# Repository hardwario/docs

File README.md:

# HARDWARIO Documentation

Technical documentation for HARDWARIO products and services —
[docs.hardwario.com](https://docs.hardwario.com). Built with
[Docusaurus 3](https://docusaurus.io). A multi-instance site: each product has its
own doc set served under `/<product>/`.

## Tech stack

- **Docusaurus 3** — React + MDX static site generator
- **Multi-instance docs** — one `@docusaurus/plugin-content-docs` instance per product
- **Algolia DocSearch** — site-wide search (index `hardwario`)
- **Cloudflare Workers** — hosting (static assets, auto-deploy via Workers Builds)

## Develop

```bash
npm install        # first time / after dependency changes (Node 18+)
npm start          # dev server → http://localhost:3000, hot reload
npm run build      # production build → build/ (fails on broken links)
npm run serve      # serve the production build locally
npm run clear      # clear the Docusaurus cache
```

## Project structure

```
docusaurus.config.js     # site config: presets, plugin instances, navbar, footer, Algolia, theme
sidebars-<product>.js    # one sidebar per product instance
<product>/               # one content folder per product, served at /<product>/:
                         #   chester, sticker, ember, fiber, gauger, tapper, tower,
                         #   cloud, cloud-new, apps, milesight, glider, rakwireless
src/
  pages/index.js         # custom homepage
  css/custom.css         # global styles / CSS variables
static/                  # assets; reference images by absolute path (/img/…)
                         #   incl. static/_redirects (same-domain slug redirects)
wrangler.jsonc           # Cloudflare Worker config — serves build/ as static assets
```

The main preset is the `chester` instance; the others are configured in the
`plugins` array of `docusaurus.config.js`. See the `docusaurus-sites` skill in the
website-admin repo for the multi-instance details.

## Content

- Docs are **Markdown/MDX** inside the relevant `<product>/` directory — identify
  the right folder first, then preserve frontmatter.
- Add new pages to the matching `sidebars-<product>.js`.
- Internal links are relative within a product; cross-product links use absolute
  paths (e.g. `/cloud/api`). **Broken internal links fail the build**
  (`onBrokenLinks: 'throw'`).
- Images live in `static/`, referenced as `/img/…`; the ideal-image and
  image-zoom plugins handle optimization and click-to-zoom.
- Match the existing technical, concise style and consistent product terminology.

### Adding a new product doc set
1. Create `<newproduct>/` at the repo root.
2. Create `sidebars-<newproduct>.js` from an existing one.
3. Add a `@docusaurus/plugin-content-docs` instance in `docusaurus.config.js`.
4. Add a navbar entry under `themeConfig.navbar.items`.
5. Add `introduction.md` as the entry point.

## Search

Algolia DocSearch, configured in `docusaurus.config.js` (`themeConfig.algolia`,
index `hardwario`). Contextual search is disabled — search spans all products.

## Deployment

Hosted on **Cloudflare Workers** (static assets) — **pushing to `main` auto-deploys**
(Workers Builds runs `npm run build` then `npx wrangler deploy`, serving `build/`).
After a push, confirm the live URL returns 200.
`editUrl` in `docusaurus.config.js` points "Edit this page" links at this repo.

---

Part of the [HARDWARIO websites](https://github.com/hardwario/website-admin) —
managed from the **website-admin** control repo (shared Claude Code commands,
skills, and environment). Content licensed under [CC BY-SA 4.0](LICENSE).

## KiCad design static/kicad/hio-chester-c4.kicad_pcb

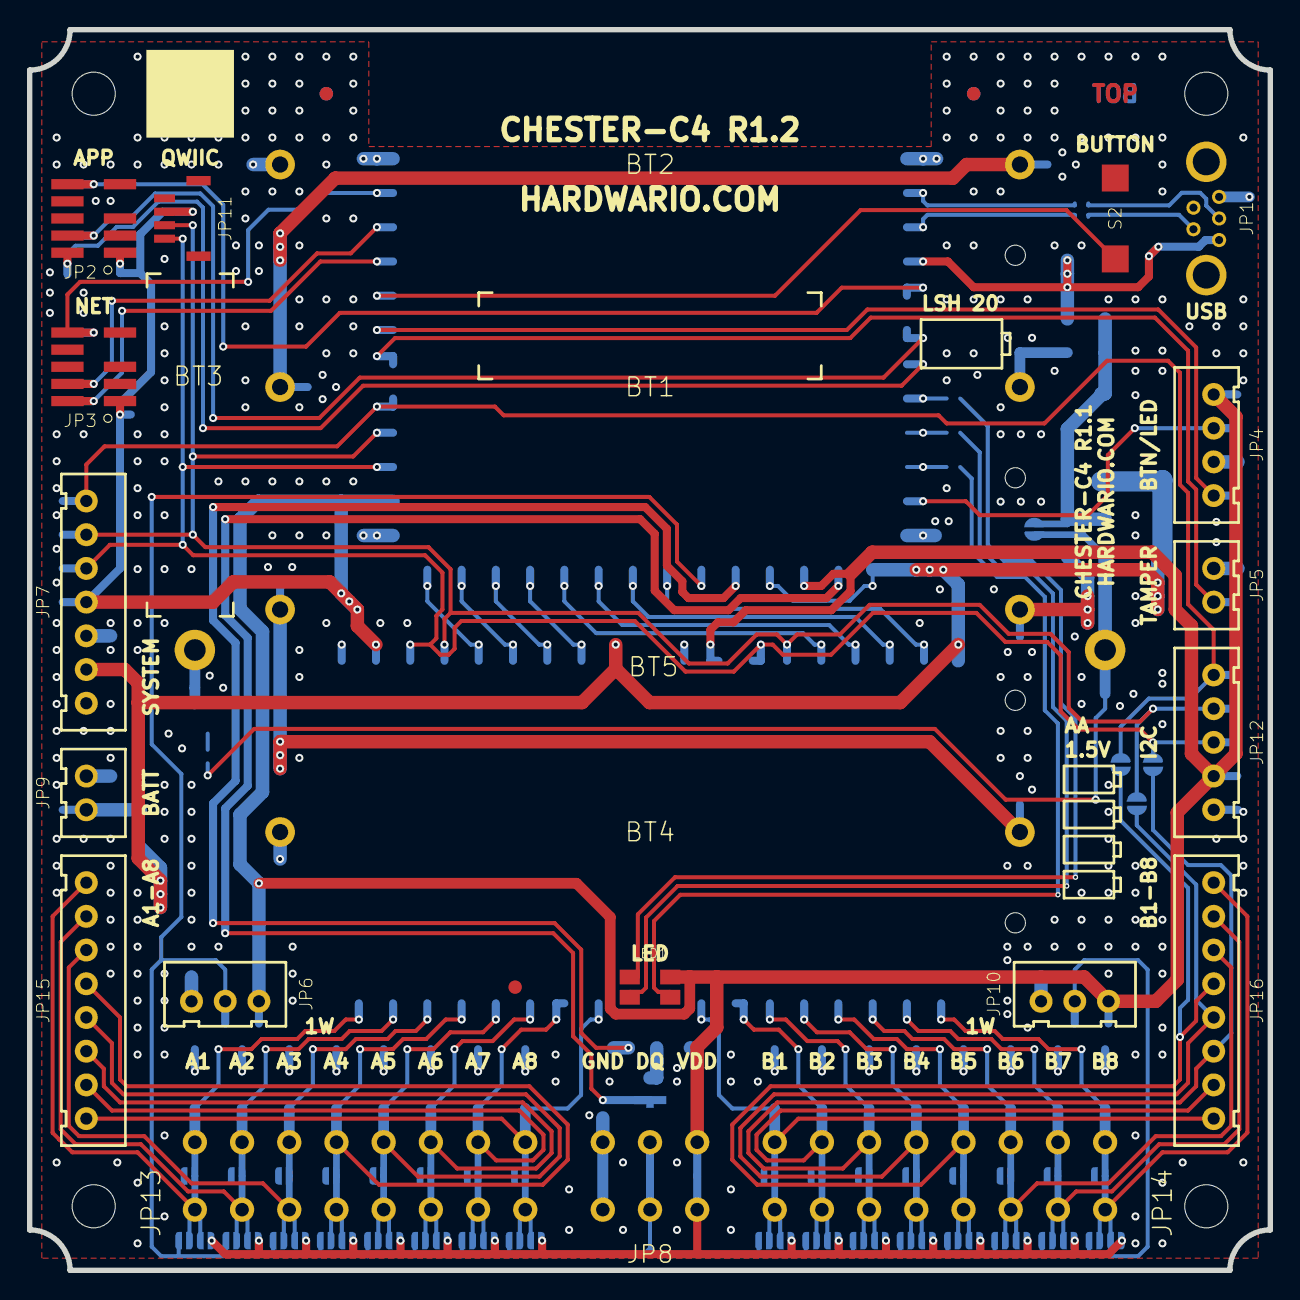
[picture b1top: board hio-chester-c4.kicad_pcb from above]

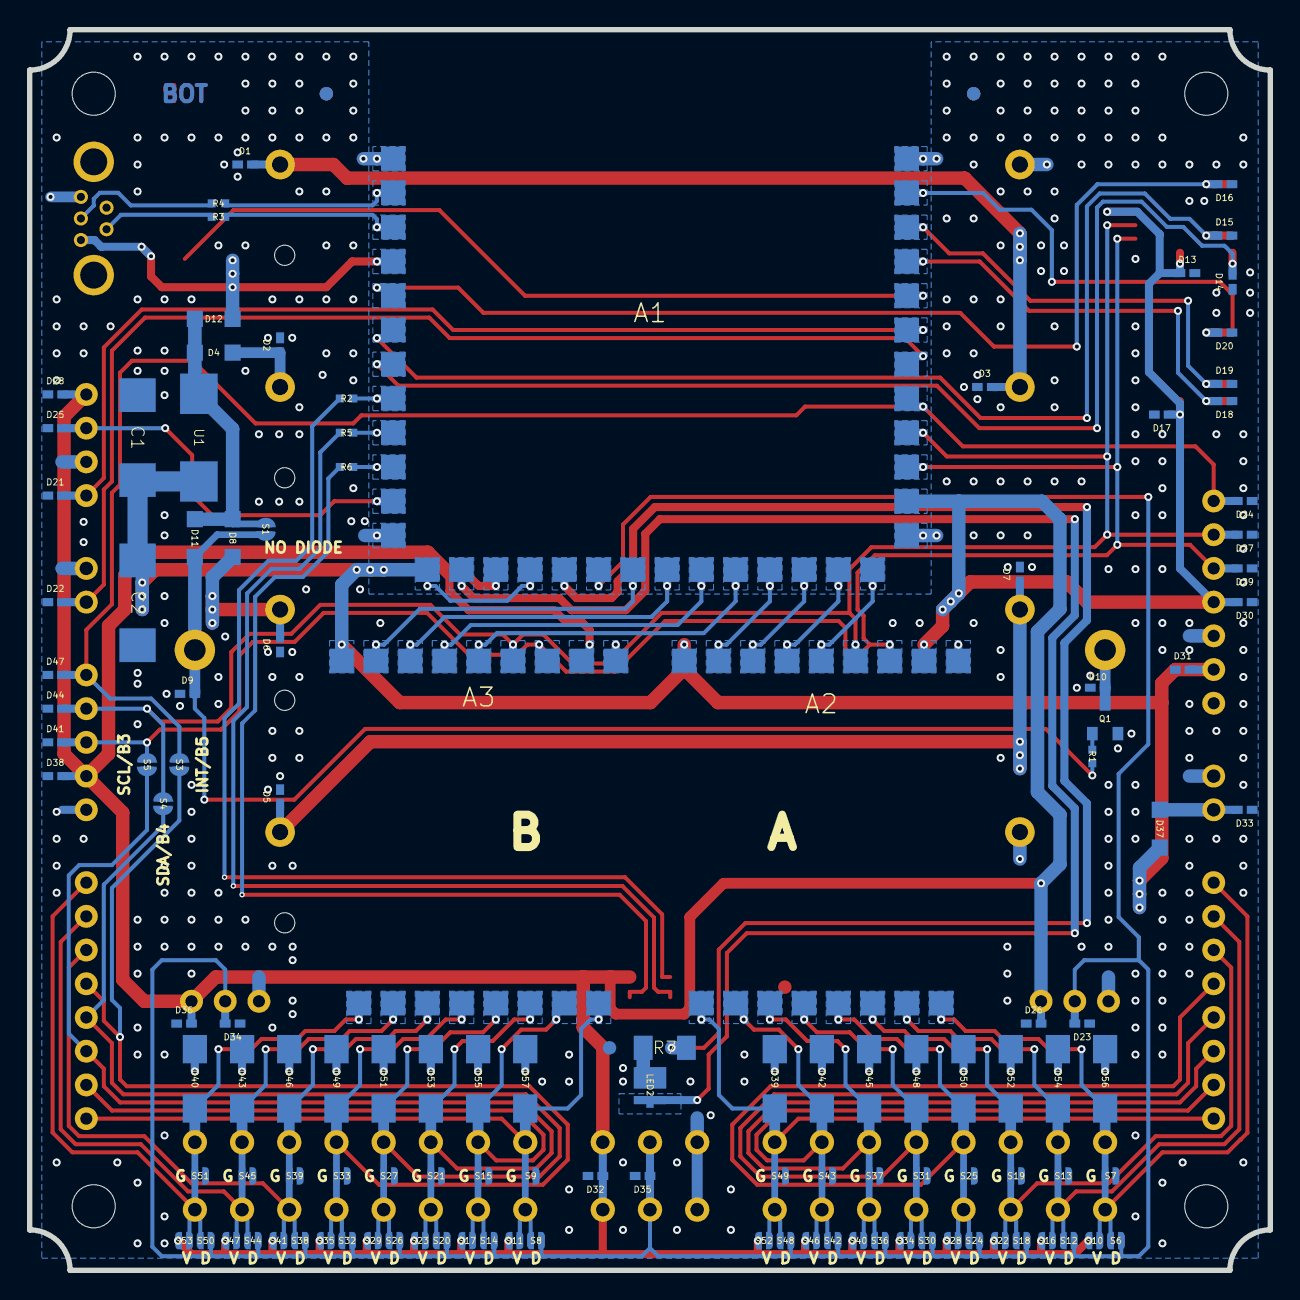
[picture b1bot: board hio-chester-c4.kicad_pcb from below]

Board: 2 copper layers, 92.0 x 92.0 mm, 159 parts (127 on the bottom side), 64 nets.

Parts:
@HOLE0, @HOLE1, @HOLE2, @HOLE3: (no value)
A1: CHESTER-U1; CHESTER-U-NO-STENCIL
A2, A3: CHESTER-X-NO-SPRING
BT1, BT2, BT3, BT4: KEYSTONE-1015; KEYSTONE-1015_R
BT5: BULGIN-BX0037; BULGIN-BX0037-NH_T
C1, C2: 220uF/10V; CAPACITOR-7343-D_R
D1, D2, D3, D5, D6, D7, D9, D10, D33: PESD5V0U1BB; PESDX_R
D4, D8, D11, D12, D37: PMEG6010ELR; SOD-123W_R
D13, D14, D15, D16, D17, D18, D19, D20, D21, D22, D23, D24, D25, D26, D27, D28, D29, D30, D32, D34, D35, D36, D38, D41, D44, D47: PESD3V3U1UB; PESDX_R
D31: PESD5V0X1UAB; PESDX_R
D39, D40, D42, D43, D45, D46, D48, D49, D50, D51, D52, D53, D54, D55, D56, D57: SMA6J28A; SMA6J_R
FD1, FD2, FD3, FD4, FD5, FD6: FIDUCIAL; FIDUCIAL-1MM
FRAME1: FRAME-SCH/A4L-BRD/A4L-HARDWARIO; FRAME-A3L-HARDWARIO
JP1: 651005136421; WE-USB-651005136421_T
JP2, JP3: BCH-P-SMT-1.27MM-2X5-E07
JP4: JST-B4B-XH-A; JST-B4B-XH-A_T
JP5, JP9: JST-B2B-XH-A; JST-B2B-XH-A_T
JP6, JP10: JST-B3B-XH-A; JST-B3B-XH-A_T
JP7: JST-B7B-XH-A; JST-B7B-XH-A_T
JP8: PTSA-1.5/3-3.5-Z; PHOENIX-PTSA-1.5_3-3.5-Z_T
JP11: BM04B-SRSS-TB; JST-BM04B-SRSS-TB
JP12: JST-B5B-XH-A; JST-B5B-XH-A_T
JP13, JP14: PTSA-1.5/8-3.5-Z; PHOENIX-PTSA-1.5_8-3.5-Z_T
JP15, JP16: JST-B8B-XH-A; JST-B8B-XH-A_T
LED1: 3528RYG-10; 3528RYG-10_R
LED2: JK3030AWT-P-H50EA; JK3030AWT
Q1: PMV30UN2; SOT-23_R
R1: 1k; RESISTOR-0402_R
R2, R5: 820R; RESISTOR-0402_R
R3, R4: 27R; RESISTOR-0402_R
R6: 330R; RESISTOR-0402_R
R7: 5R6; RESISTOR-1206_R
S1: NO DIODE; SOLDER-BRIDGE-1.5MM
S2: SKPMAPE010; SKPMAPE010_R
S3: INT; SOLDER-BRIDGE-1.5MM
S4: SDA; SOLDER-BRIDGE-1.5MM
S5: SCL; SOLDER-BRIDGE-1.5MM
S6, S7, S8, S9, S10, S11, S12, S13, S14, S15, S16, S17, S18, S19, S20, S21, S22, S23, S24, S25, S26, S27, S28, S29, S30, S31, S32, S33, S34, S35, S36, S37, S38, S39, S40, S41, S42, S43, S44, S45, S46, S47, S48, S49, S50, S51, S52, S53: S-SOLDER-BRIDGE-1.5MM-S; SOLDER-BRIDGE-1.5MM-S
U1: T1A; SCHURTER-3404.0114.22_R
U$1: QR-PRINT

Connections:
+V: A1.13, A1.16, A2.9A, A3.9A, C1.A, C2.A, D31.1, D37.C, JP7.6, U1.2
A1: A2.1A, D56.C, JP13.8A, JP13.8B, JP15.1, S6.1, S7.2, S10.1
A2: A2.2A, D54.C, JP13.7A, JP13.7B, JP15.2, S12.1, S13.2, S16.1
A3: A2.3A, D52.C, JP13.6A, JP13.6B, JP15.3, S18.1, S19.2, S22.1
A4: A2.4A, D50.C, JP13.5A, JP13.5B, JP15.4, S24.1, S25.2, S28.1
A5: A2.5A, D48.C, JP13.4A, JP13.4B, JP15.5, S30.1, S31.2, S34.1
A6: A2.6A, D45.C, JP13.3A, JP13.3B, JP15.6, S36.1, S37.2, S40.1
A7: A2.7A, D42.C, JP13.2A, JP13.2B, JP15.7, S42.1, S43.2, S46.1
A8: A2.8A, D39.C, JP13.1A, JP13.1B, JP15.8, S48.1, S49.2, S52.1
B1: A3.1A, D57.C, JP14.8A, JP14.8B, JP16.1, S8.1, S9.2, S11.1
B2: A3.2A, D55.C, JP14.7A, JP14.7B, JP16.2, S14.1, S15.2, S17.1
B3: A3.3A, D53.C, JP14.6A, JP14.6B, JP16.3, S5.2, S20.1, S21.2, S23.1
B4: A3.4A, D51.C, JP14.5A, JP14.5B, JP16.4, S4.2, S26.1, S27.2, S29.1
B5: A3.5A, D49.C, JP14.4A, JP14.4B, JP16.5, S3.2, S32.1, S33.2, S35.1
B6: A3.6A, D46.C, JP14.3A, JP14.3B, JP16.6, S38.1, S39.2, S41.1
B7: A3.7A, D43.C, JP14.2A, JP14.2B, JP16.7, S44.1, S45.2, S47.1
B8: A3.8A, D40.C, JP14.1A, JP14.1B, JP16.8, S50.1, S51.2, S53.1
GND: A1.1, A1.12, A1.27, A1.38, A2.17A, A3.17A, BT2.M1, BT4.M1, C1.C, C2.C, D1.1, D2.1, D3.1, D5.1, D6.1, D7.1, D9.1, D10.1, D13.2, D14.2, D15.2, D16.2, D17.2, D18.2, D19.2, D20.2, D21.2, D22.2, D23.2, D24.2, D25.2, D26.2, D27.2, D28.2, D29.2, D30.2, D31.2, D32.2, D33.1, D34.2, D35.2, D36.2, D38.2, D39.A, D40.A, D41.2, D42.A, D43.A, D44.2, D45.A, D46.A, D47.2, D48.A, D49.A, D50.A, D51.A, D52.A, D53.A, D54.A, D55.A, D56.A, D57.A, JP1.5, JP2.3, JP2.5, JP3.3, JP3.5, JP4.2, JP5.2, JP6.1, JP7.5, JP8.3A, JP8.3B, JP9.1, JP10.1, JP11.1, JP12.1, Q1.2, S2.1, S7.1, S9.1, S13.1, S15.1, S19.1, S21.1, S25.1, S27.1, S31.1, S33.1, S37.1, S39.1, S43.1, S45.1, S49.1, S51.1
GND13: A1.19, A3.10A
GND15: A1.20, A3.11A
GND20: A1.21, A3.12A
GND21: A1.22, A3.13A
GND22: A1.23, A2.10A
GND23: A1.24, A2.11A
GND24: A1.25, A2.12A
GND49: A1.26, A2.13A
GND50: A1.32, D22.1, JP5.1
GND51: A1.33, D21.1, JP4.1
GND52: A1.34, S2.2
GND53: A1.35, D18.1, JP3.2
GND54: A1.36, D19.1, JP3.4
GND55: A1.37, D20.1, JP3.10
GND56: A1.18, D23.1, D34.1, D35.1, JP6.2, JP8.2A, JP8.2B, JP10.2, S6.2, S8.2, S12.2, S14.2, S18.2, S20.2, S24.2, S26.2, S30.2, S32.2, S36.2, S38.2, S42.2, S44.2, S48.2, S50.2
GND57: A1.11, D25.1, JP4.3
GND58: A1.5, D16.1, JP2.10
GND59: A1.6, D15.1, JP2.4
GND60: A1.7, D14.1, JP2.2
GND61: A1.2, R4.2
GND62: A1.3, R3.2
GND63: A1.4, D12.A, JP1.1
GND64: JP1.3, R4.1
GND65: D33.2, D37.A, JP9.2
GND66: BT1.M1, BT2.P1, D1.2, D3.2
GND67: BT3.M1, BT4.P1, D5.2, D7.2
GND68: BT3.P1, D6.2, D8.A
GND69: BT1.P1, D2.2, D4.A
GND70: BT5.P, D9.2, D11.A, R1.2, S1.1
GND71: JP1.2, R3.1
GND72: A1.14, LED2.A
GND73: LED2.C, R7.2
GND74: D4.C, D8.C, D11.C, D12.C, S1.2, U1.1
GND75: Q1.1, R1.1
GND76: BT5.M, D10.2, Q1.3
GND77: A1.17, R7.1
INT: A1.31, D24.1, D47.1, JP7.1, JP12.5, S3.1
LED_G: A1.9, R5.1
LED_G_C: LED1.2, R5.2
LED_R: A1.8, R2.1
LED_R_C: LED1.1, R2.2
LED_Y: A1.10, R6.1
LED_Y_C: LED1.3, R6.2
SCL: A1.29, A2.15A, A3.15A, D29.1, D41.1, JP7.3, JP11.4, JP12.3, S5.1
SDA: A1.30, A2.14A, A3.14A, D27.1, D44.1, JP7.2, JP11.3, JP12.4, S4.1
VDD: A1.15, A1.28, A2.16A, A3.16A, D13.1, D17.1, D26.1, D28.1, D30.1, D32.1, D36.1, D38.1, JP2.1, JP3.1, JP4.4, JP6.3, JP7.4, JP8.1A, JP8.1B, JP10.3, JP11.2, JP12.2, LED1.4, S10.2, S11.2, S16.2, S17.2, S22.2, S23.2, S28.2, S29.2, S34.2, S35.2, S40.2, S41.2, S46.2, S47.2, S52.2, S53.2

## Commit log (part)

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2025-01-23 CHESTER: Deploy v3.1.0 FWs
2025-01-23 CHESTER: Deploy v3.1.0 FWs (#124)
2025-01-25 Update to docusaurus version 3
2025-01-25 Remove package-lock.json
2025-01-25 Update package-lock
2025-01-25 FIBER: Update broken file
2025-01-27 Move CHESTER BLE Tag subsystem documentation to Common functionality from Chester Clime
2025-02-11 CHESTER: Update Vodafone EU28+2 table (#127)
2025-02-14 CHESTER: Fix Vodafone EU28+2 table
2025-02-17 chester: Add chester-x13 docs
2025-02-17 Update EMBER intial configuration guide
    - Rewrite of the document to fit style and improve readability
    - Renamed from initialization.md to initial-configuration.md
    - Added some tips
2025-02-17 update EMBER Initial configuration
2025-02-20 chester: Add chester-x13 and chester-x14 pages
2025-02-20 CHESTER: Update board definitions for ncs2.9.0
2025-02-20 CHESTER: Update windows intructions
2025-02-20 CHESTER: Update board definitions for ncs2.9.0 & windows instructions (#130)
    * CHESTER: Update board definitions for ncs2.9.0
    * CHESTER: Update windows intructions
2025-02-21 CHESTER: Add U1 KiCad symbol and footprint (#131)
2025-02-24 Fix int-pin.png
2025-02-25 Fix colors
    - Fix mistake, where recolor of buttons caused recolor of whole secondary class
2025-02-25 Default to dark mode
2025-02-25 Correct Store Links at TOWER Components
2025-02-28 CHESTER: Fix LoRaWAN modem release v1.4.1
2025-02-28 CHESTER: Make LTE v2 firmware default
2025-02-28 CHESTER: Fix firmware chapter links (#136)
2025-02-28 CHESTER: Update Zephyr SDK instructions to v0.17.0
2025-03-03 extension modules: Fix maximum voltage
2025-03-11 CHESTER: Deploy v3.2.0 FWs
2025-03-20 CHESTER Control: Counter time
2025-03-21 CHESTER: Deploy v3.2.1 FWs
2025-03-24 Update homepage fiber image
2025-04-04 gauger: Add GAUGER documentation
2025-04-04 Rescale gauger image
2025-04-04 Add missing values to data table
2025-04-10 CHESTER: Deploy v3.2.2 FWs
2025-04-17 chester: catalog-applications: control: Add counter delta to example json
2025-04-22 CHESTER: Deploy v3.2.3 FWs
2025-04-22 CHESTER: Deploy v3.2.4 FWs
2025-04-25 Ember RouterOS oficial page
2025-04-29 CHESTER: Supported sensors - Init version
2025-04-29 Add apps
2025-05-06 chester: Add list of supported modbus sensors
2025-05-06 supported_sensors: Add Lambrecht meteo
2025-05-07 Supported sensors add table with IWM-TX5
2025-05-08 CHIRPSTACK Update config to IOT lora
2025-05-08 EMBER Hardware preparation
2025-05-11 Add TAPPER section
2025-05-12 EMBER External antenna
2025-05-25 Update TAPPER docs to match version 1.0.3
    - Add Installation
    - Add Usage
    - Rewrite Introduction
    - Moved MQTT API to a separate file, this is yet to be finished
2025-05-26 Add MQTT specification for TAPPER
2025-05-26 Update API Specs
    - Remove redundant topics from Request response
2025-05-27 Update ubuntu runner in GH Actions
2025-05-27 Update algoliasearch version in GH actions
2025-05-27 Add debug to GH Actions
2025-05-27 Update for debug
2025-05-27 Move pipenv install
2025-05-27 Move delete script to tmp folder
2025-05-27 Move script to different folder
2025-05-27 Add pipenv again
2025-05-27 Move fully to python
2025-05-27 Final update of CI
2025-05-27 Update python version
2025-05-27 Update python code
2025-05-27 Add dependencies
2025-05-27 Remove deprecated CI file
2025-05-27 Add TLS
2025-05-28 Add information about pipx path esnuring
2025-05-28 Format TAPPER with prettier
2025-05-28 Change algolia search
2025-05-28 Go back to previous algolia solution
2025-05-31 Fix typos in TAPPER
2025-05-31 Reorder TAPPER sidebar
2025-05-31 Reodred TAPPER Sidebar
2025-05-31 Polish TAPPER
2025-06-02 Improve TAPPER hardware spec table
2025-06-05 Update TAPPER Docs
    - Add power consumption
    - Fix formatting
2025-06-11 Fix TAPPER Client Usage heading levels
2025-06-16 EMBER Default password for login
2025-06-16 Add MQTT outside connection configuration to EMBER Chirpstack v4 Installation guide
2025-06-18 Add sticker boilerplate
2025-06-19 CHESTER Update LTE configuration
2025-06-19 Add LTE config to EMBER initial config (#143)
2025-06-20 Add dbus dependencies
2025-06-20 Improve TAPPER Config and API readability, add detail
2025-06-20 Move TAPPER behind FIBER
2025-06-24 catalog-applications: control: Merge text from input docs
2025-06-26 Add SSH security tip to TAPPER installation
2025-06-26 Add the TAPPER security tips to the intro page
2025-06-26 Fix mistake in CLI help
2025-06-27 TAPPER: Add WiFi passphrase hashing into security enhancements
2025-07-10 Add Ubidots Category
2025-07-14 Update EMBER docs
2025-07-16 CELLULAR NETWORK: Update for prefers Vodafone and 1nce
2025-07-21 Apps-Ubidots
2025-07-22 Chester - supported sensors image edit, Ubidots - headline edit
2025-07-22 Supported Sensors - adding Carlo Gavazzi EMxx
2025-07-23 Add Ubidots cloud/deivce; update Modbus docs
2025-07-23 Add Ubidots guide images and cloud/device; update Modbus docs
2025-07-30 Oprava odkazu na Schneider elektroměr
2025-07-30 Update link to schneider electric energy analyzer
2025-07-30 Supported Senzors - oprava odkazu+oprava příkazů
2025-08-06 TAPPER: Update installation.md
2025-08-06 TAPPER: Update installatio.md
2025-08-12 Fixing Apps/Supported Senzors doc, adding youtube tutorials
2025-08-25 Apps - indexes update, videos upload, cloud v2 migration
2025-08-26 TAPPER: WIP on installation
2025-08-28 Adding Sticker doc
2025-09-08 Sticker - Developer Access (Debug Mode)
2025-09-08 Sticker - debug mode - header change
2025-09-16 TAPPER: WIP - update docs
2025-09-17 Thingsboard, apps index fix, code block fix, sticker nfc architecture
2025-09-19 Chester - Common Functionality - tag - magnet
2025-09-24 Apps - Video Tutorials (ChirpStack, ThingsBoard, Ubidots fix)
2025-10-01 Milesigth docs + New navigation bar
2025-10-06 Ubidots - html canvas docs
2025-10-06 Apps - The Things Network, Cloud - Variables, Ubidots - new structure, Synthetic Variables
2025-10-06 Ubidots - links update
2025-10-08 Chester wm-bus - commands update
2025-10-15 Chirpstack tutorials update, video tutorials embed update, cloud variables fix
2025-10-19 Mikrotik - broken links fix
2025-10-19 Chirpstack - config broken link fix
2025-10-27 Homepage update, Chester - getting started - first step etc.
2025-10-27 Chester - fisrt step - adding chester - scaning QR code option
2025-11-03 Fix Tapper Format
2025-11-07 Hardwario terminal, Sticker input config -> Sticker input wiring
2025-11-10 Chester - First Step, Milesight
2025-11-16 Update FIBER docs
2025-11-19 The Things Stack - Video Guide page fix
2025-11-19 Chester - mobile and lorawan networks links fix
2025-12-03 CHESTER: Deploy v3.5.0 FWs
2025-12-05 CHESTER: Improve code generator
2025-12-05 CHESTER: Improve code generator (#173)
    * CHESTER: Improve code generator
    * CHESTER: Fix radon link
2025-12-08 chester: catalog: Update Clime firmware to v3.5.1
    - Update all Clime variants to v3.5.1
    - Remove Clime 1W (moved to legacy)
    - Add Clime Radon variant
    - Remove standalone Radon app (moved to legacy)
2025-12-10 ChirpStack v4, The Things Stack, LoRaWan Public, Milesight sensors update
2025-12-10 Milesight AM300 series links fix
2025-12-10 Milesight link fix
2025-12-29 Chester - tts, chirpstack ; tts - docs update
2026-01-02 Sticker/Ember - getting started, LoraWan; Navbar Update
2026-01-14 Update JSON examples for CHESTER and STICKER
2026-01-14 Fix JSON formatting in CHESTER documentation across multiple files
2026-01-30 SMART DEVICES - RAKwireless docs, Chester-x12 extension module, CHESTER Serial
2026-01-30 Fix links in RAKwireless gateways documentation for accurate navigation
2026-01-30 Fix links in RAKwireless gateways documentation for RAK7268V2 and RAK7289V2
2026-01-30 Fix link typo for RAK7289V2 in gateways documentation
2026-01-31 CHESTER - X12 extension image fix
2026-02-02 CHESTER - Scale, quick start fix, catalog app table
2026-02-02 Catalog apps - table fix
2026-02-03 APPS - Chirpstack - Fix links for MikroTik
2026-02-05 Update Milesight FT101 documentation for clarity and accuracy
2026-02-05 Updated milesight-ft101 manual
2026-02-09 Update initial configuration guide to quick start format
2026-02-11 Adding CHESTER Motion, TB - User Roles doc update
2026-02-19 CHESTER Motion/Serial update, ThingsBoard - user groups/roles
2026-02-20 Update access instructions for EMBER - LAN
    Clarified the initial access instructions for EMBER concerning the LAN port
2026-02-20 Revise hardware description for antennas and ports
    Updated antenna description and clarified LAN/WAN port locations.
2026-02-26 Update slug and title for initial configuration
2026-02-27 Revise CHESTER Current documentation and commands
    Updated the documentation for CHESTER Current to reflect changes in v3.5.1., including command structure, configuration parameters, and calibration procedures.
2026-03-05 Added Hall Effect Sensor Calibration instructions
    Added section on Hall Effect Sensor Calibration including calibration logic, theoretical parameters, and CLI configuration commands.
2026-03-17 Update LTE section: generic APN, SIM PIN unlock, and verification
    - Replace Onomondo-specific APN with generic 'internet' APN and a tip to change it per carrier
    - Add SIM PIN unlock instructions (enter PIN and permanently disable PIN)
    - Add LTE connection verification steps (monitor and ping)
2026-03-18 CHESTER - First Step Update, TB docs UpdateRefactor code structure for improved readability and maintainability
2026-03-18 Update hardware documentation and settings: clarify WAN connectivity, add new web fetch permissions, and enhance climate module features
2026-03-18 Fix image path case sensitivity in hardware description
2026-04-01 Add changelog sections to multiple platform documentation files
2026-04-07 Add CHESTER Control 8Ch Z to catalog applications table
2026-04-14 Add catalog page links for CHESTER Scale variants
2026-04-14 Fix Serial variant anchors to match RS-232/RS-485 naming
2026-04-14 Update common functionality with new SDK features
2026-04-15 Rename changelog title and improve firmware builds table layout
2026-04-15 Update changelog slug to shorter URL path
2026-04-15 Fix image path formatting in HARDWARIO Terminal documentation
2026-04-20 Notification Manager - Access levels, Thingsboard - password change
2026-04-30 Thingsboard - User managind manual
2026-04-30 Update sidebar configuration for user management in Thingsboard
2026-05-05 Cloud-new docs, Changelog update, TB link
2026-05-05 Remove unnecessary paragraph tags from JSON example in CHESTER Current documentation
2026-05-12 Clarify Python PATH option label in NFC Configurator setup
2026-05-13 TB Public link docs - Refactor code structure for improved readability and maintainability
2026-05-15 Add General settings section and PoE warning to UG65 docs
2026-05-22 Add GLIDER docs, sidebar, and homepage tile
2026-05-22 DOCS - ThingsBoard example dashboard embed
2026-05-22 Docs - remove numbering from ThingsBoard sidebar items
2026-05-27 Docs - add section on creating and sharing device groups in user management
2026-06-09 Docs - add guide for embedding ThingsBoard dashboards
2026-06-09 Docs - add section on embedding a single widget in ThingsBoard dashboards
2026-06-13 Correct header for password change instructions
2026-06-16 chester: scale: Update Scale and Scale Z firmware to v3.5.5
    Bump CHESTER Scale and Scale Z to firmware v3.5.5 in the Cloud v2
    firmware table, add a v3.5.5 changelog entry, and document the new
    runtime CHESTER-X3 slot B detection (single firmware covers both
    single-slot and dual-slot hardware).
2026-06-22 Thingsboard - integrations, CHESTER - hardware schematics fix etc, orno-or-we-516 - configuration of chester
2026-06-23 Add Update LTE section to EMBER Hotspot configuration
2026-06-24 Docs - update changelogs for SDK v3.5.5 and related applications; enhance introduction with links to changelogs
2026-06-28 Add Cloudflare Workers configuration
